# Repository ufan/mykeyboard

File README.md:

# A collection of designed keyboards #
## Features
All keyboards are powered by [zmk](https://zmk.dev/) with following design goals:
- portability
- minimalism
- ergonomic
- yet still powerful

## Super-powerful trackball firmware
- [youtube trackball demo](https://www.youtube.com/watch?v=7J-NTVMHwWQ&t=86s)
- [pmw3610_breakout pcb](https://github.com/ufan/pmw3610_breakout)
- [firmware support](https://github.com/ufan/zmk/tree/ptdevice-refactor)

# 42-key classic Corne-Pro with EPD display

# 34-key Sweep-Pro with horizontal encoders

# 32-key Blade with a mini-trackball and a touchbar

# Customizable logo display

# Wireless charging option

# Tenting support

# Extensible

# 3D-printed concave/convex keycaps

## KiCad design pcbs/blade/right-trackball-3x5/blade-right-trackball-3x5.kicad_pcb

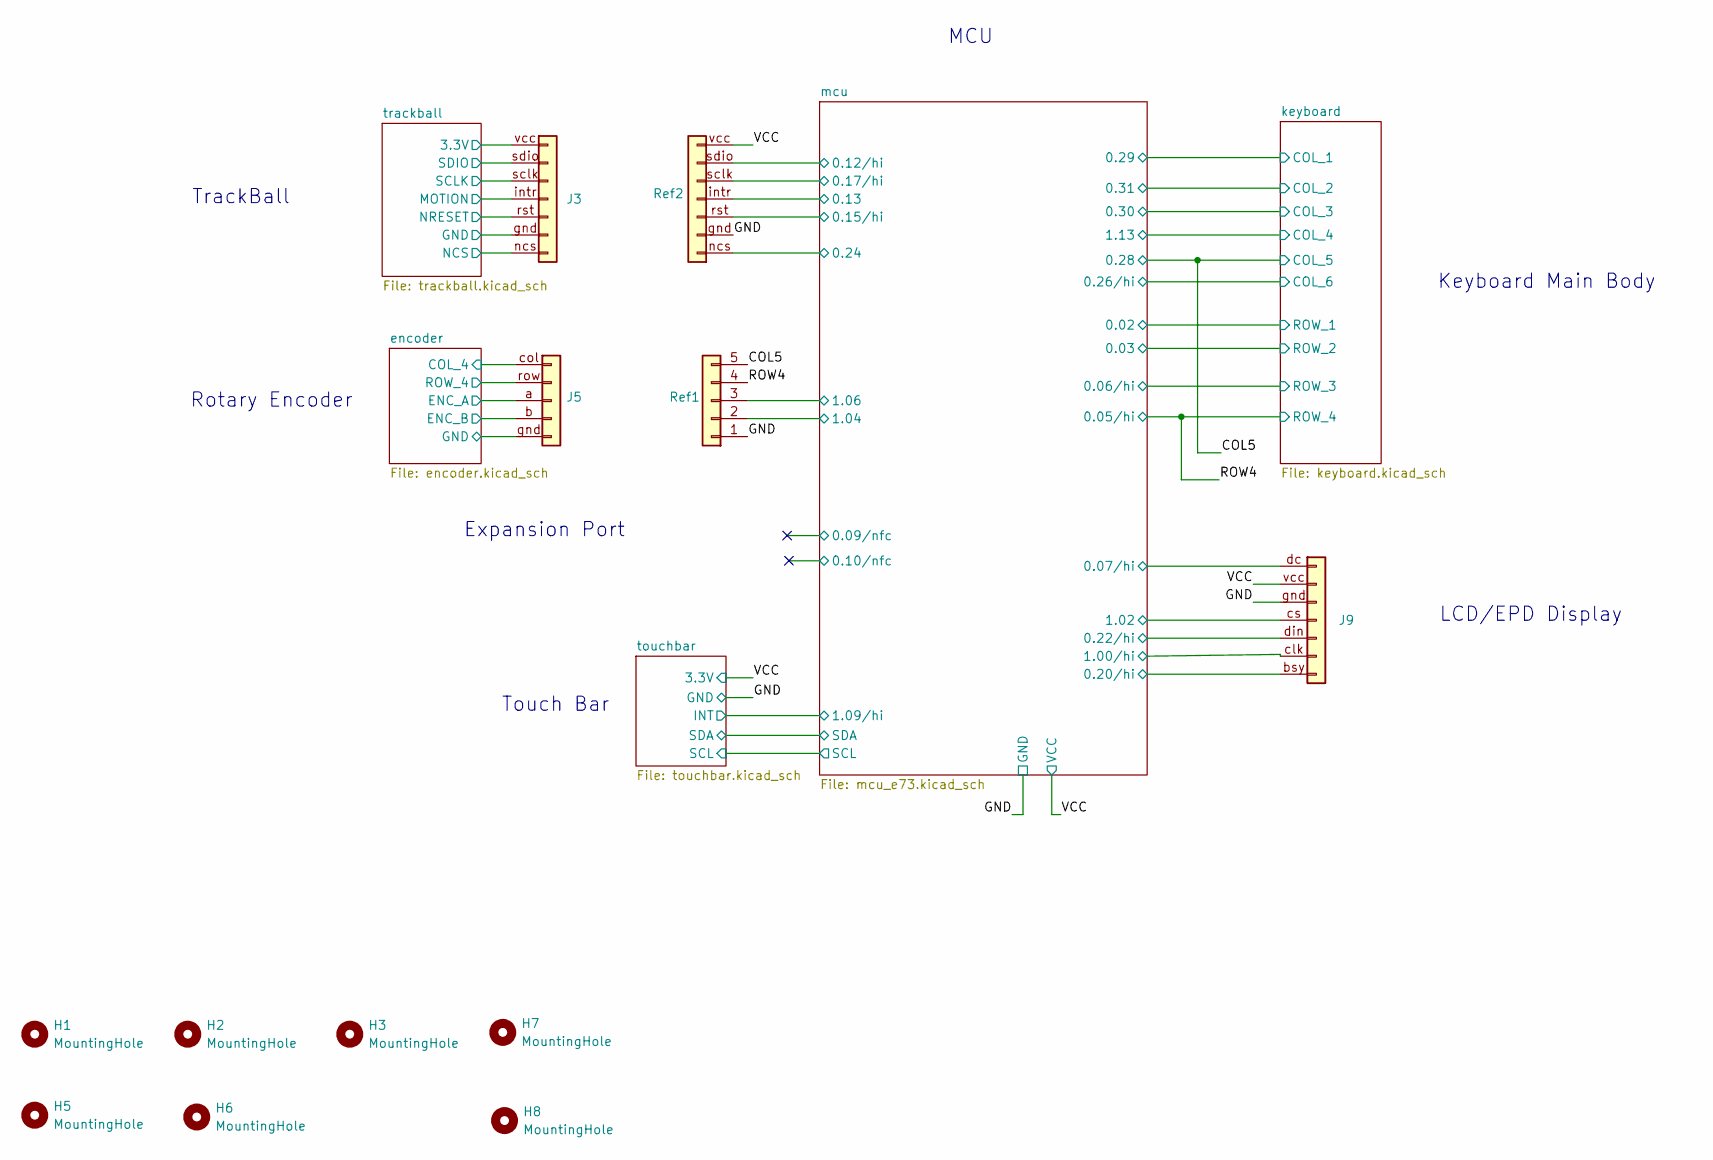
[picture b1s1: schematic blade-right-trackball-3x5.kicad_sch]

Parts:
H1, H2, H3, H5, H6, H7: MountingHole; MountingHole_3.2mm_M3_DIN965
H8: MountingHole; MountingHole_2mm
J3: Conn_01x07; PMW3610-Ref-Male
J5: Conn_01x05; Panasonic_EVQWGD001_Ref_Male
J9: Conn_Display_general; Conn_Display_MountHole
Ref1: Conn_01x05; Panasonic_EVQWGD001_Ref
Ref2: Conn_1x07; PMW3610-Ref

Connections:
/COL5: Ref1.5; also elsewhere on the board
/ROW4: Ref1.4; also elsewhere on the board
/VCC: J9.vcc, Ref2.vcc; also elsewhere on the board
/encoder/COL_4: J5.col; also elsewhere on the board
/encoder/ENC_A: J5.a; also elsewhere on the board
/encoder/ENC_B: J5.b; also elsewhere on the board
/encoder/GND: J5.gnd; also elsewhere on the board
/encoder/ROW_4: J5.row; also elsewhere on the board
/mcu/0.07/hi: J9.dc; also elsewhere on the board
/mcu/0.12/hi: Ref2.sdio; also elsewhere on the board
/mcu/0.13: Ref2.intr (motion); also elsewhere on the board
/mcu/0.15/hi: Ref2.rst; also elsewhere on the board
/mcu/0.17/hi: Ref2.sclk; also elsewhere on the board
/mcu/0.20/hi: J9.bsy; also elsewhere on the board
/mcu/0.22/hi: J9.din; also elsewhere on the board
/mcu/0.24: Ref2.ncs; also elsewhere on the board
/mcu/1.00/hi: J9.clk; also elsewhere on the board
/mcu/1.02: J9.cs; also elsewhere on the board
/mcu/1.04: Ref1.2; also elsewhere on the board
/mcu/1.06: Ref1.3; also elsewhere on the board
/trackball/3.3V: J3.vcc; also elsewhere on the board
/trackball/GND: J3.gnd; also elsewhere on the board
/trackball/MOTION: J3.intr (motion); also elsewhere on the board
/trackball/NCS: J3.ncs; also elsewhere on the board
/trackball/NRESET: J3.rst; also elsewhere on the board
/trackball/SCLK: J3.sclk; also elsewhere on the board
/trackball/SDIO: J3.sdio; also elsewhere on the board
GND: J9.gnd, Ref1.1, Ref2.gnd; also elsewhere on the board

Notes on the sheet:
Touch Bar
Rotary Encoder
LCD/EPD Display
Keyboard Main Body
Expansion Port
TrackBall
MCU

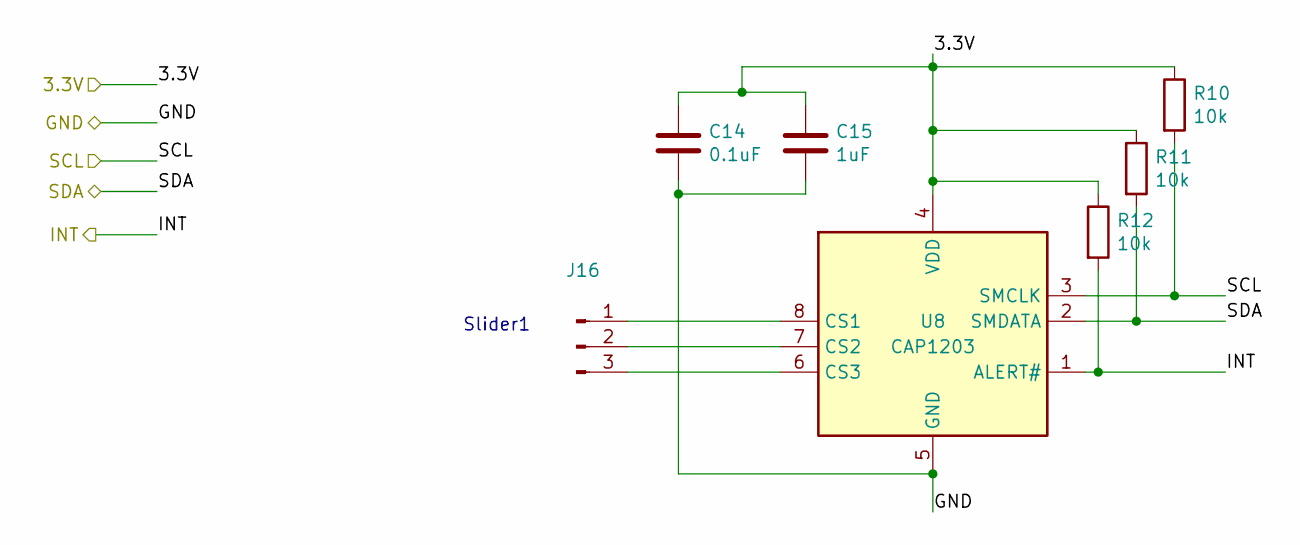
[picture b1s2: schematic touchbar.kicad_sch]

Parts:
C14: 0.1uF; C_0603_1608Metric
C15: 1uF; C_0603_1608Metric
J16: Conn_01x03_Male; TouchSlider-3_36x12mm
R10, R11, R12: 10k; R_0603_1608Metric
U8: CAP1203; SOIC-8_3.9x4.9mm_P1.27mm

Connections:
/VCC: C14.1, C15.1, R10.1, R11.1, R12.1, U8.4 (VDD); also elsewhere on the board
/mcu/SCL: R10.2, U8.3 (SMCLK); also elsewhere on the board
/mcu/SDA: R11.2, U8.2 (SMDATA); also elsewhere on the board
/touchbar/INT: R12.2, U8.1 (ALERT#); also elsewhere on the board
GND: C14.2, C15.2, U8.5 (GND); also elsewhere on the board
unnamed: J16.1, U8.8 (CS1)
unnamed: J16.2, U8.7 (CS2)
unnamed: J16.3, U8.6 (CS3)

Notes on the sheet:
Slider1

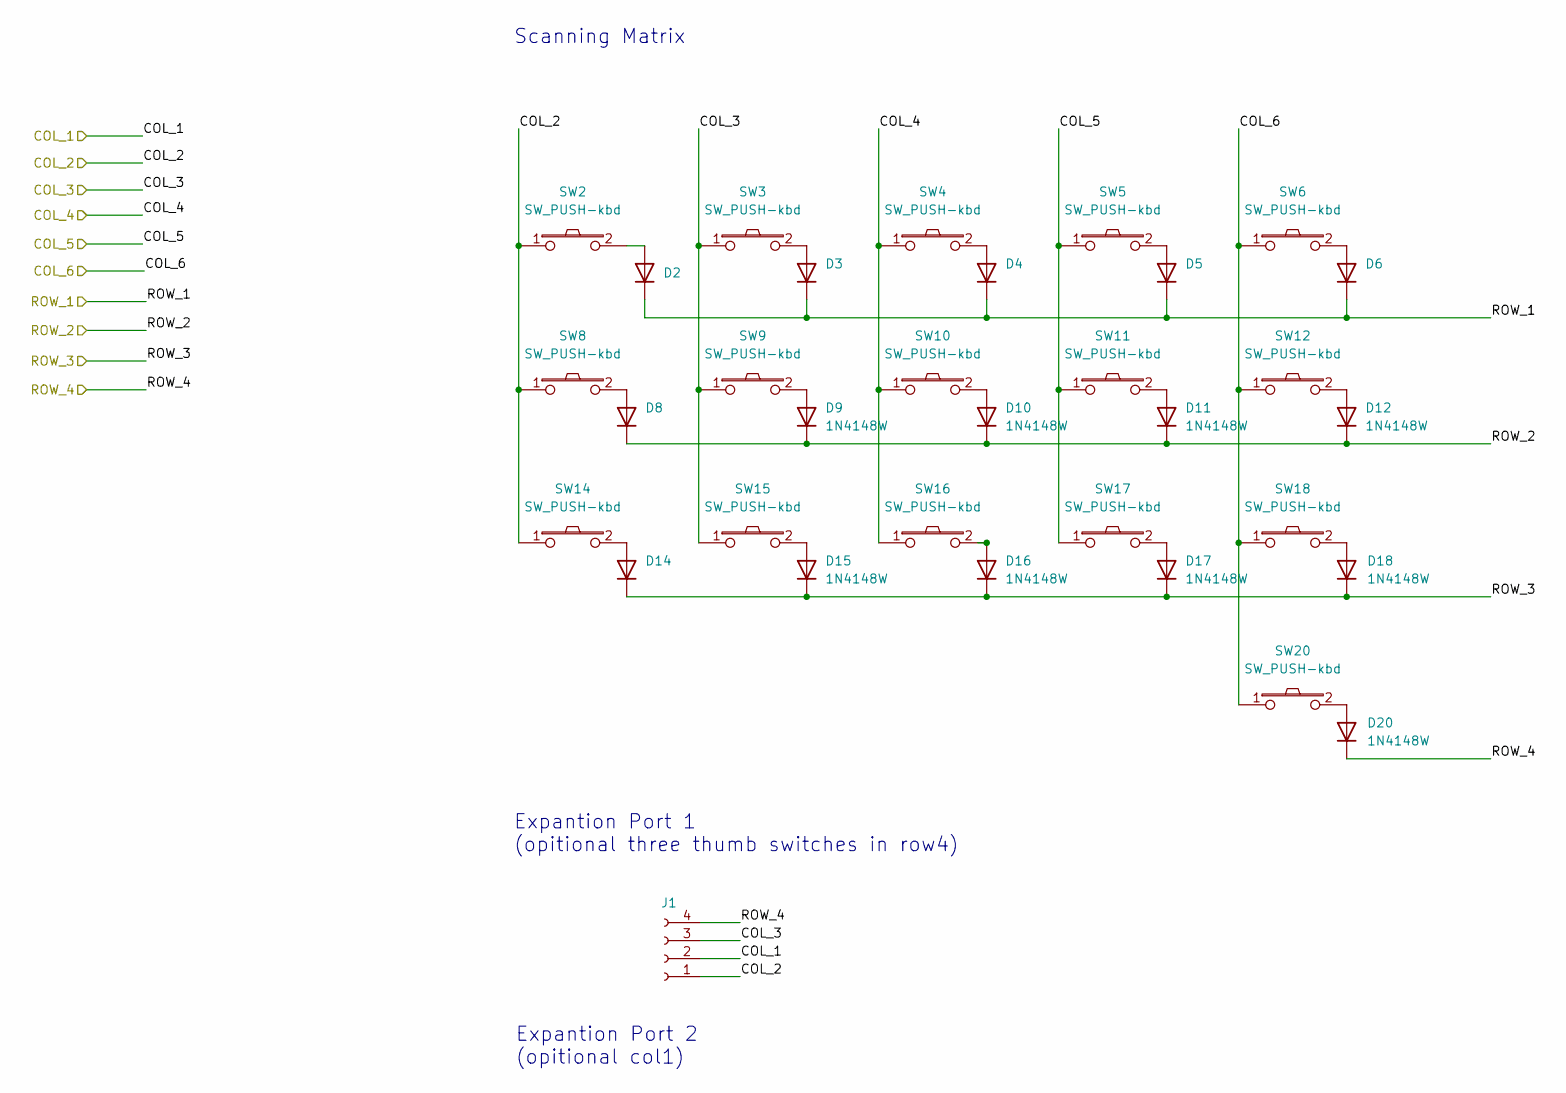
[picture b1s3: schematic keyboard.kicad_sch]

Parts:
D2, D3, D4, D5, D6, D8, D9, D10, D11, D12, D14, D15, D16, D17, D18, D20: 1N4148W; Diode
J1: expantion1; Magnetic-PogoPin-1x04-Female
SW2, SW3, SW4, SW5, SW6, SW8, SW9, SW10, SW11, SW12, SW14, SW15, SW16, SW17, SW18, SW20: SW_PUSH-kbd; Kailh_Choc_Hotplug

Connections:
/COL5: SW5.1, SW11.1, SW17.1; also elsewhere on the board
/ROW4: D20.1 (K), J1.4; also elsewhere on the board
/keyboard/COL_1: J1.2; also elsewhere on the board
/keyboard/COL_2: J1.1, SW2.1, SW8.1, SW14.1; also elsewhere on the board
/keyboard/COL_3: J1.3, SW3.1, SW9.1, SW15.1; also elsewhere on the board
/keyboard/COL_4: SW4.1, SW10.1, SW16.1; also elsewhere on the board
/keyboard/COL_6: SW6.1, SW12.1, SW18.1, SW20.1; also elsewhere on the board
/keyboard/ROW_1: D2.1 (K), D3.1 (K), D4.1 (K), D5.1 (K), D6.1 (K); also elsewhere on the board
/keyboard/ROW_2: D8.1 (K), D9.1 (K), D10.1 (K), D11.1 (K), D12.1 (K); also elsewhere on the board
/keyboard/ROW_3: D14.1 (K), D15.1 (K), D16.1 (K), D17.1 (K), D18.1 (K); also elsewhere on the board
unnamed: D2.2 (A), SW2.2
unnamed: D3.2 (A), SW3.2
unnamed: D4.2 (A), SW4.2
unnamed: D5.2 (A), SW5.2
unnamed: D6.2 (A), SW6.2
unnamed: D8.2 (A), SW8.2
unnamed: D9.2 (A), SW9.2
unnamed: D10.2 (A), SW10.2
unnamed: D11.2 (A), SW11.2
unnamed: D12.2 (A), SW12.2
unnamed: D14.2 (A), SW14.2
unnamed: D15.2 (A), SW15.2
unnamed: D16.2 (A), SW16.2
unnamed: D17.2 (A), SW17.2
unnamed: D18.2 (A), SW18.2
unnamed: D20.2 (A), SW20.2

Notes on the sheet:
Scanning Matrix
Expantion Port 2 (opitional col1)
Expantion Port 1 (opitional three thumb switches in row4)

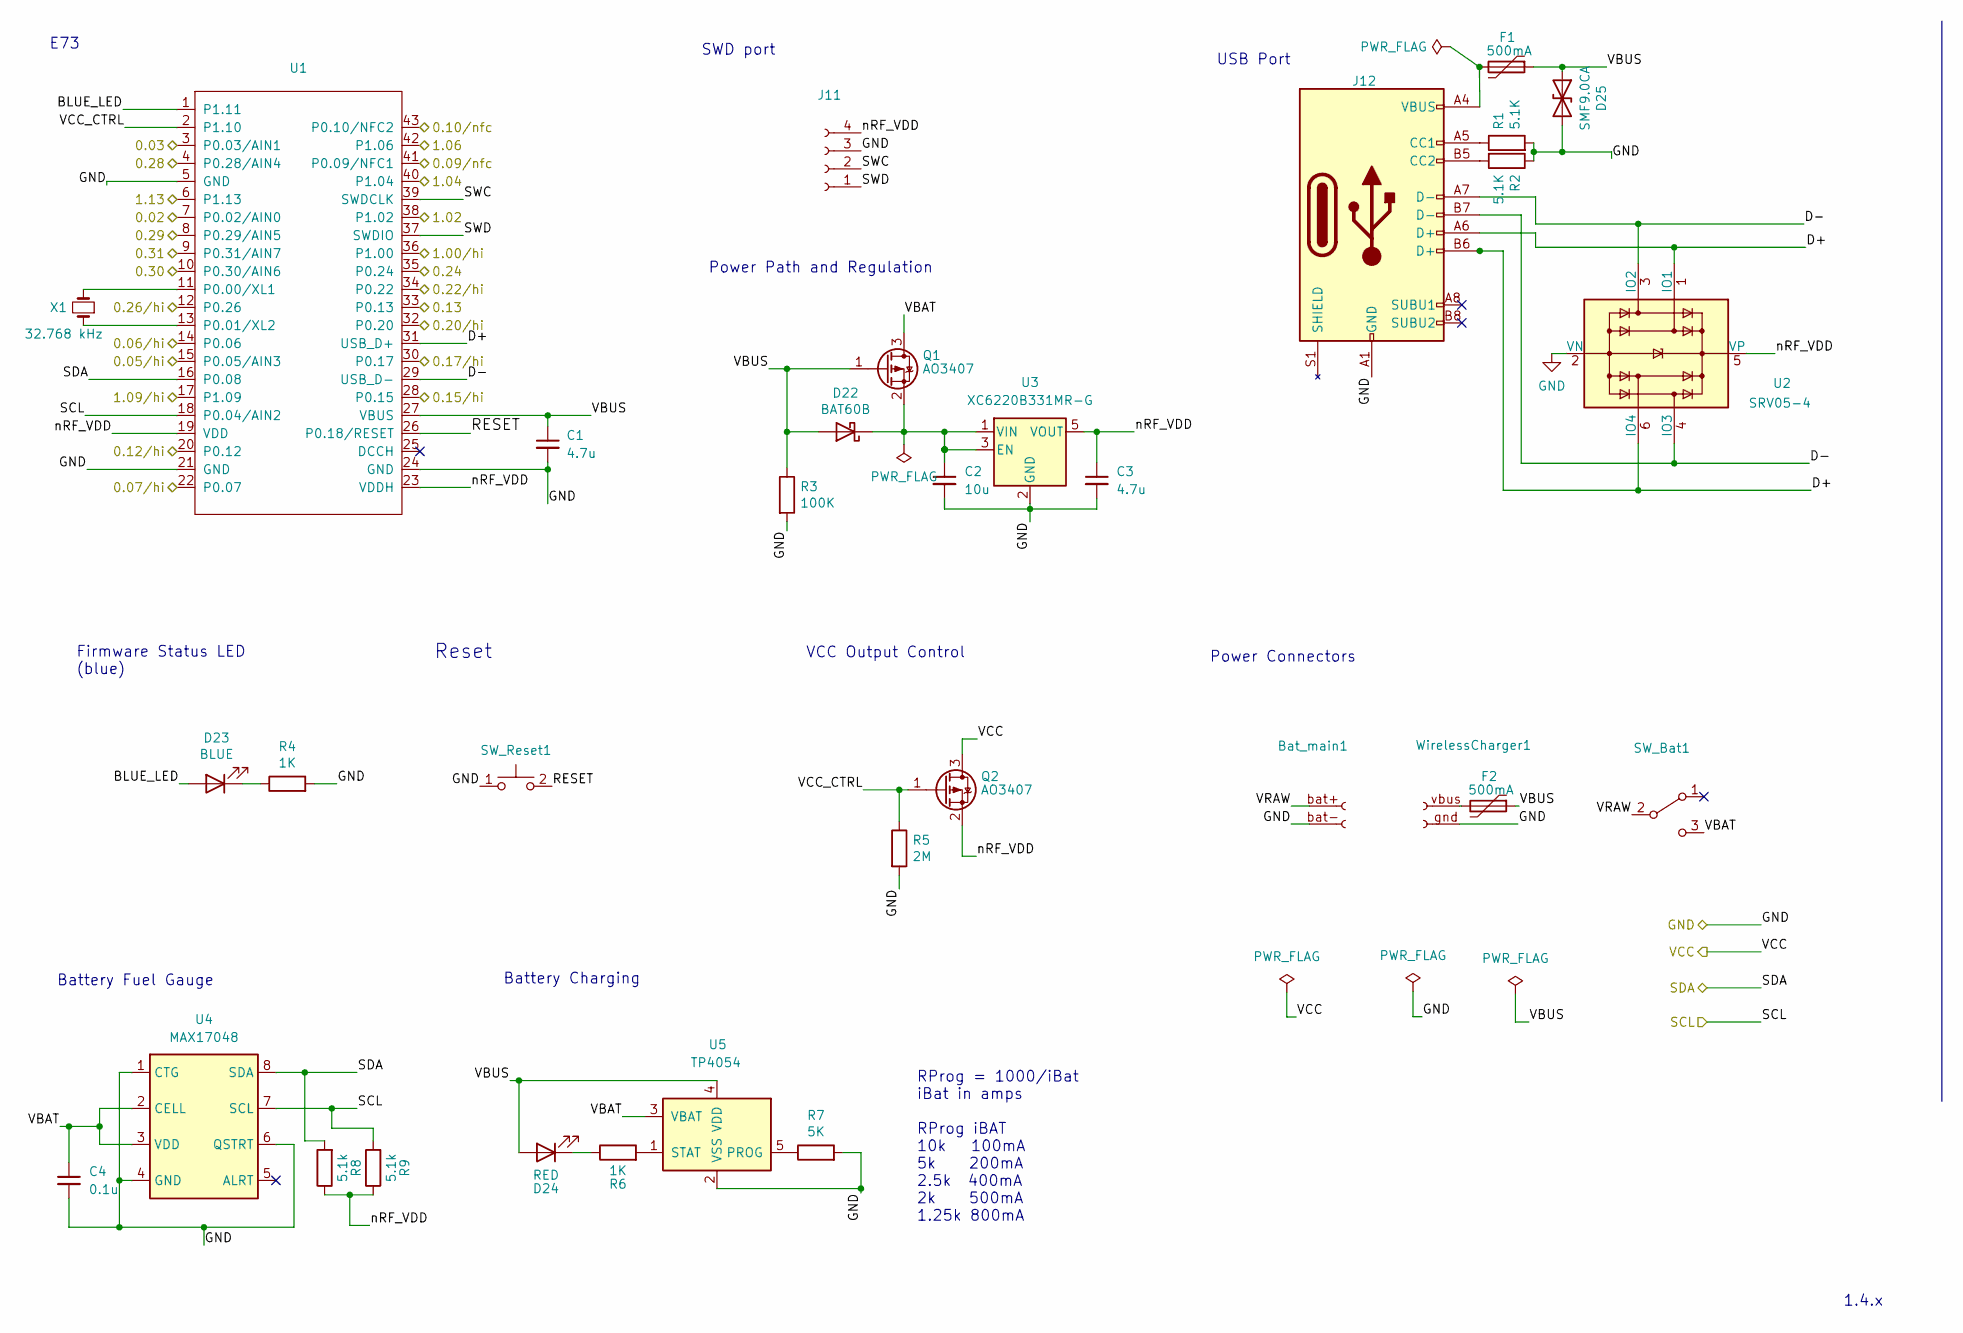
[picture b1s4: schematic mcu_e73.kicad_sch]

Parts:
Bat_main1: Conn_Battery_solderable; JST_ACH_BM02B-ACHSS-GAN-ETF_1x02-1MP_P1.20mm_Vertical
C1, C3: 4.7u; C_0603_1608Metric
C2: 10u; C_0603_1608Metric
C4: 0.1u; C_0603_1608Metric
D22: BAT60B; D_SOD-323
D23: BLUE; LED_0603_1608Metric
D24: RED; LED_0603_1608Metric
D25: SMF9.0CA; D_SOD-123F; Part Name Bidirectional Diode; LCSC Part C435473
F1, F2: 500mA; Fuse_1206_3216Metric; Part Name Polyfuse; LCSC Part C151162
J11: Conn_01x04_Female; PinHeader_1x04_P2.54mm_Vertical
J12: USB-C USB 2.0 MC-372; nrfmicro_USB-C_C168688
Q1, Q2: AO3407; SOT-23
R1, R2: 5.1K; R_0603_1608Metric
R3: 100K; R_0603_1608Metric
R4, R6: 1K; R_0603_1608Metric
R5: 2M; R_0603_1608Metric
R7: 5K; R_0603_1608Metric
R8, R9: 5.1k; R_0603_1608Metric
SW_Bat1: SW_Battery-kbd; SW_BSI10
SW_Reset1: SW_RESET-kbd; SW_Reset_vertical
U1: E73-2G4M08S1C; E73-2G4M08S1C-52840
U2: SRV05-4; Part Name TVS Diode Array; LCSC Part C558418
U3: XC6220B331MR-G; SOT-23-5
U4: MAX17048; MAX17048-TDFN-8-1EP_2x2mm_P0.5mm_EP0.8x1.2mm
U5: TP4054; SOT-23-5
WirelessCharger1: Conn_01x02_Female; JST_ACH_BM02B-ACHSS-GAN-ETF_1x02-1MP_P1.20mm_Vertical
X1: 32.768 kHz; Crystal_SMD_MicroCrystal_CM9V-T1A-2Pin_1.6x1.0mm

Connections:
/COL5: U1.4 (P0.28/AIN4); also elsewhere on the board
/ROW4: U1.15 (P0.05/AIN3); also elsewhere on the board
/VCC: Q2.3 (D); also elsewhere on the board
/keyboard/COL_1: U1.8 (P0.29/AIN5); also elsewhere on the board
/keyboard/COL_2: U1.9 (P0.31/AIN7); also elsewhere on the board
/keyboard/COL_3: U1.10 (P0.30/AIN6); also elsewhere on the board
/keyboard/COL_4: U1.6 (P1.13); also elsewhere on the board
/keyboard/COL_6: U1.12 (P0.26); also elsewhere on the board
/keyboard/ROW_1: U1.7 (P0.02/AIN0); also elsewhere on the board
/keyboard/ROW_2: U1.3 (P0.03/AIN1); also elsewhere on the board
/keyboard/ROW_3: U1.14 (P0.06); also elsewhere on the board
/mcu/0.07/hi: U1.22 (P0.07); also elsewhere on the board
/mcu/0.09/nfc: U1.41 (P0.09/NFC1)
/mcu/0.10/nfc: U1.43 (P0.10/NFC2)
/mcu/0.12/hi: U1.20 (P0.12); also elsewhere on the board
/mcu/0.13: U1.33 (P0.13); also elsewhere on the board
/mcu/0.15/hi: U1.28 (P0.15); also elsewhere on the board
/mcu/0.17/hi: U1.30 (P0.17); also elsewhere on the board
/mcu/0.20/hi: U1.32 (P0.20); also elsewhere on the board
/mcu/0.22/hi: U1.34 (P0.22); also elsewhere on the board
/mcu/0.24: U1.35 (P0.24); also elsewhere on the board
/mcu/1.00/hi: U1.36 (P1.00); also elsewhere on the board
/mcu/1.02: U1.38 (P1.02); also elsewhere on the board
/mcu/1.04: U1.40 (P1.04); also elsewhere on the board
/mcu/1.06: U1.42 (P1.06); also elsewhere on the board
/mcu/BLUE_LED: D23.2 (A), U1.1 (P1.11)
/mcu/D+: J12.A6 (D+), J12.B6 (D+), U1.31 (USB_D+), U2.1 (IO1), U2.6 (IO4)
/mcu/D-: J12.A7 (D-), J12.B7 (D-), U1.29 (USB_D-), U2.3 (IO2), U2.4 (IO3)
/mcu/RESET: SW_Reset1.2, U1.26 (P0.18/RESET)
/mcu/SCL: R9.2, U1.18 (P0.04/AIN2), U4.7 (SCL); also elsewhere on the board
/mcu/SDA: R8.2, U1.16 (P0.08), U4.8 (SDA); also elsewhere on the board
/mcu/SWC: J11.2, U1.39 (SWDCLK)
/mcu/SWD: J11.1, U1.37 (SWDIO)
/mcu/VBAT: C4.1, Q1.3 (D), SW_Bat1.3 (C), U4.2 (CELL), U4.3 (VDD), U5.3 (VBAT)
/mcu/VBUS: C1.1, D22.2 (A), D24.2 (A), D25.1 (A1), F1.1, F2.1, Q1.1 (G), R3.1, U1.27 (VBUS), U5.4 (VDD)
/mcu/VCC_CTRL: Q2.1 (G), R5.1, U1.2 (P1.10)
/mcu/VRAW: Bat_main1.bat+ (Bat+), SW_Bat1.2 (B)
/mcu/nRF_VDD: C3.1, J11.4, Q2.2 (S), R8.1, R9.1, U1.19 (VDD), U1.23 (VDDH), U2.5 (VP), U3.5 (VOUT)
/touchbar/INT: U1.17 (P1.09); also elsewhere on the board
GND: Bat_main1.bat- (Bat-), C1.2, C2.2, C3.2, C4.2, D25.2 (A2), J11.3, J12.A1 (GND), R1.2, R2.1, R3.2, R4.2, R5.2, R7.2, SW_Reset1.1, U1.5 (GND), U1.21 (GND), U1.24 (GND), U2.2 (VN), U3.2 (GND), U4.1 (CTG), U4.4 (GND), U4.6 (QSTRT), U5.2 (VSS), WirelessCharger1.gnd; also elsewhere on the board
unnamed: C2.1, D22.1 (K), Q1.2 (S), U3.1 (VIN), U3.3 (EN)
unnamed: D23.1 (K), R4.1
unnamed: D24.1 (K), R6.1
unnamed: F1.2, J12.A4 (VBUS)
unnamed: F2.2, WirelessCharger1.vbus
unnamed: J12.A5 (CC1), R1.1
unnamed: J12.B5 (CC2), R2.2
unnamed: R6.2, U5.1 (STAT)
unnamed: R7.1, U5.5 (PROG)
unnamed: U1.11 (P0.00/XL1), X1.2
unnamed: U1.13 (P0.01/XL2), X1.1

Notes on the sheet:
Battery Charging
Reset
Power Path and Regulation
RProg = 1000/iBat iBat in amps RProg iBAT 10k 100mA 5k 200mA 2.5k 400mA 2k 500mA 1.25k 800mA
1.4.x
USB Port
Battery Fuel Gauge
E73
VCC Output Control
Power Connectors
SWD port
Firmware Status LED (blue)

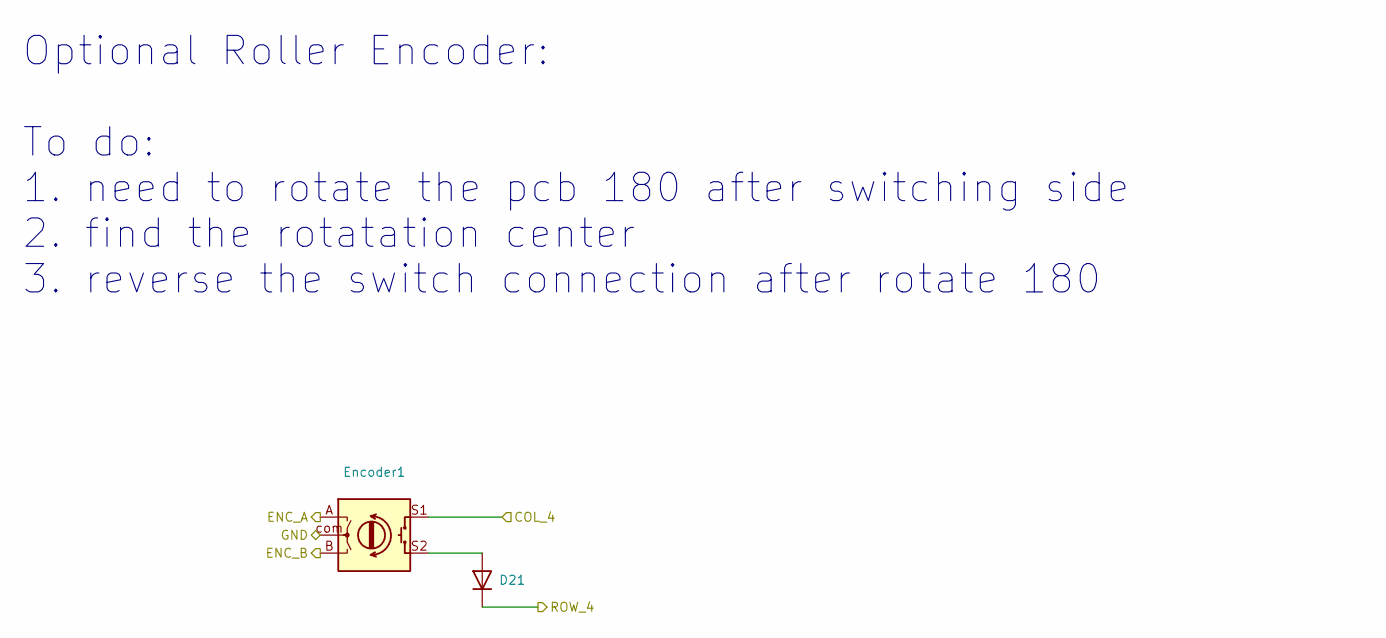
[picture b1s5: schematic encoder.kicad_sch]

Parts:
D21: 1N4148W; Diode
Encoder1: RotaryEncoder; Panasonic_EVQWGD001_Latest

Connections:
/encoder/COL_4: Encoder1.S1; also elsewhere on the board
/encoder/ENC_A: Encoder1.A; also elsewhere on the board
/encoder/ENC_B: Encoder1.B; also elsewhere on the board
/encoder/GND: Encoder1.com (COM); also elsewhere on the board
/encoder/ROW_4: D21.1 (K); also elsewhere on the board
unnamed: D21.2 (A), Encoder1.S2

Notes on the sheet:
Optional Roller Encoder: To do: 1. need to rotate the pcb 180 after switching side 2. find the rotatation center 3. reverse the switch connection after rotate 180

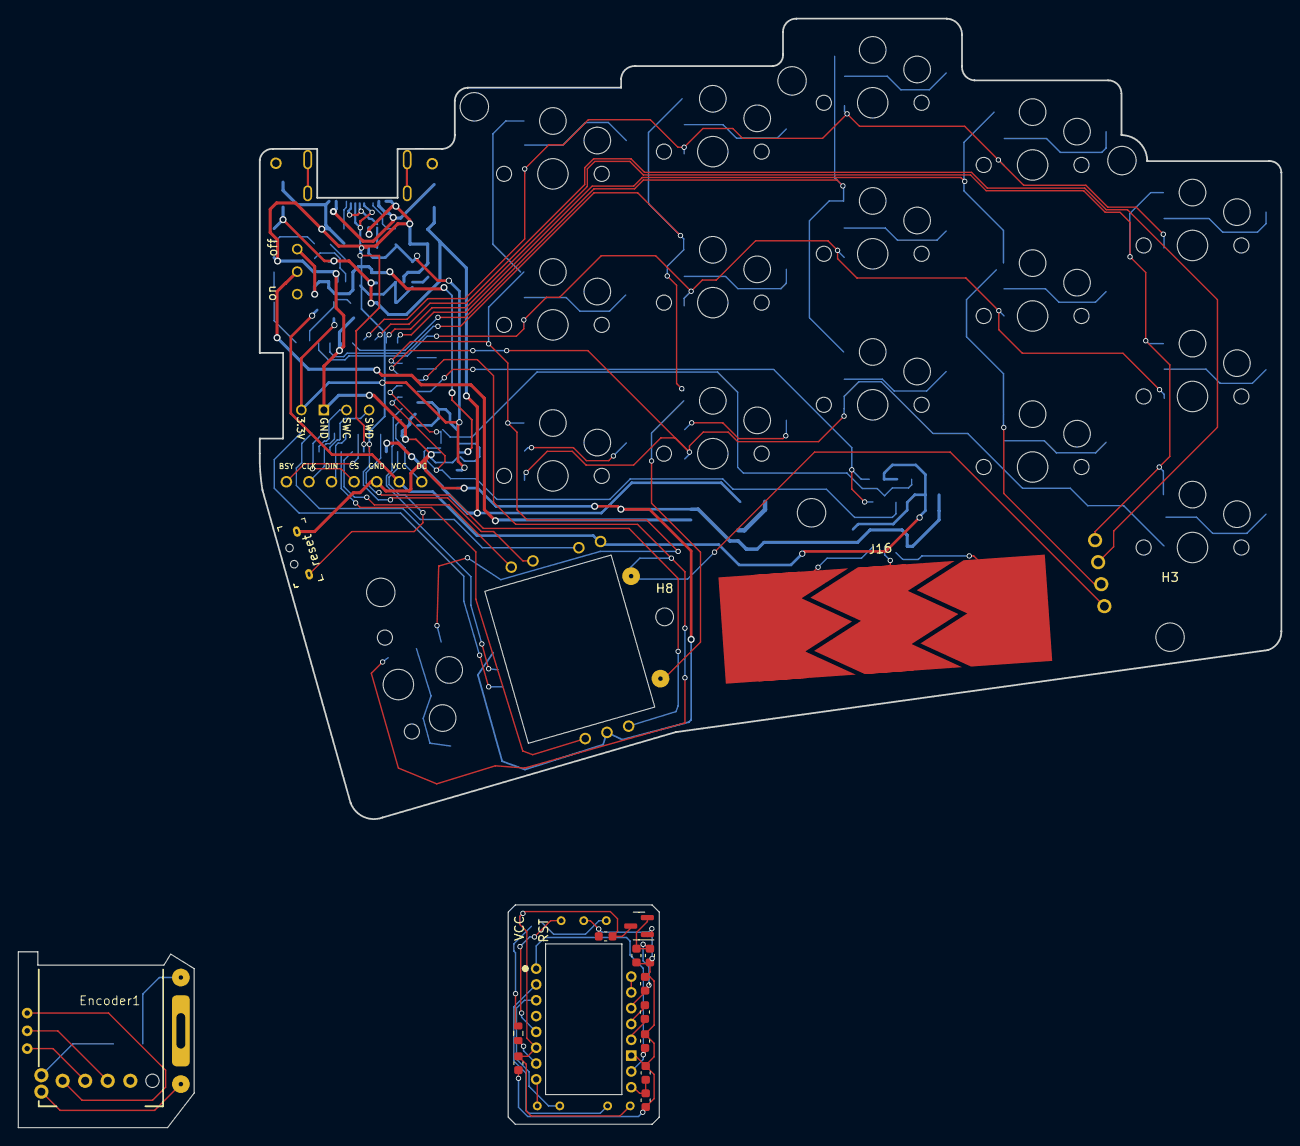
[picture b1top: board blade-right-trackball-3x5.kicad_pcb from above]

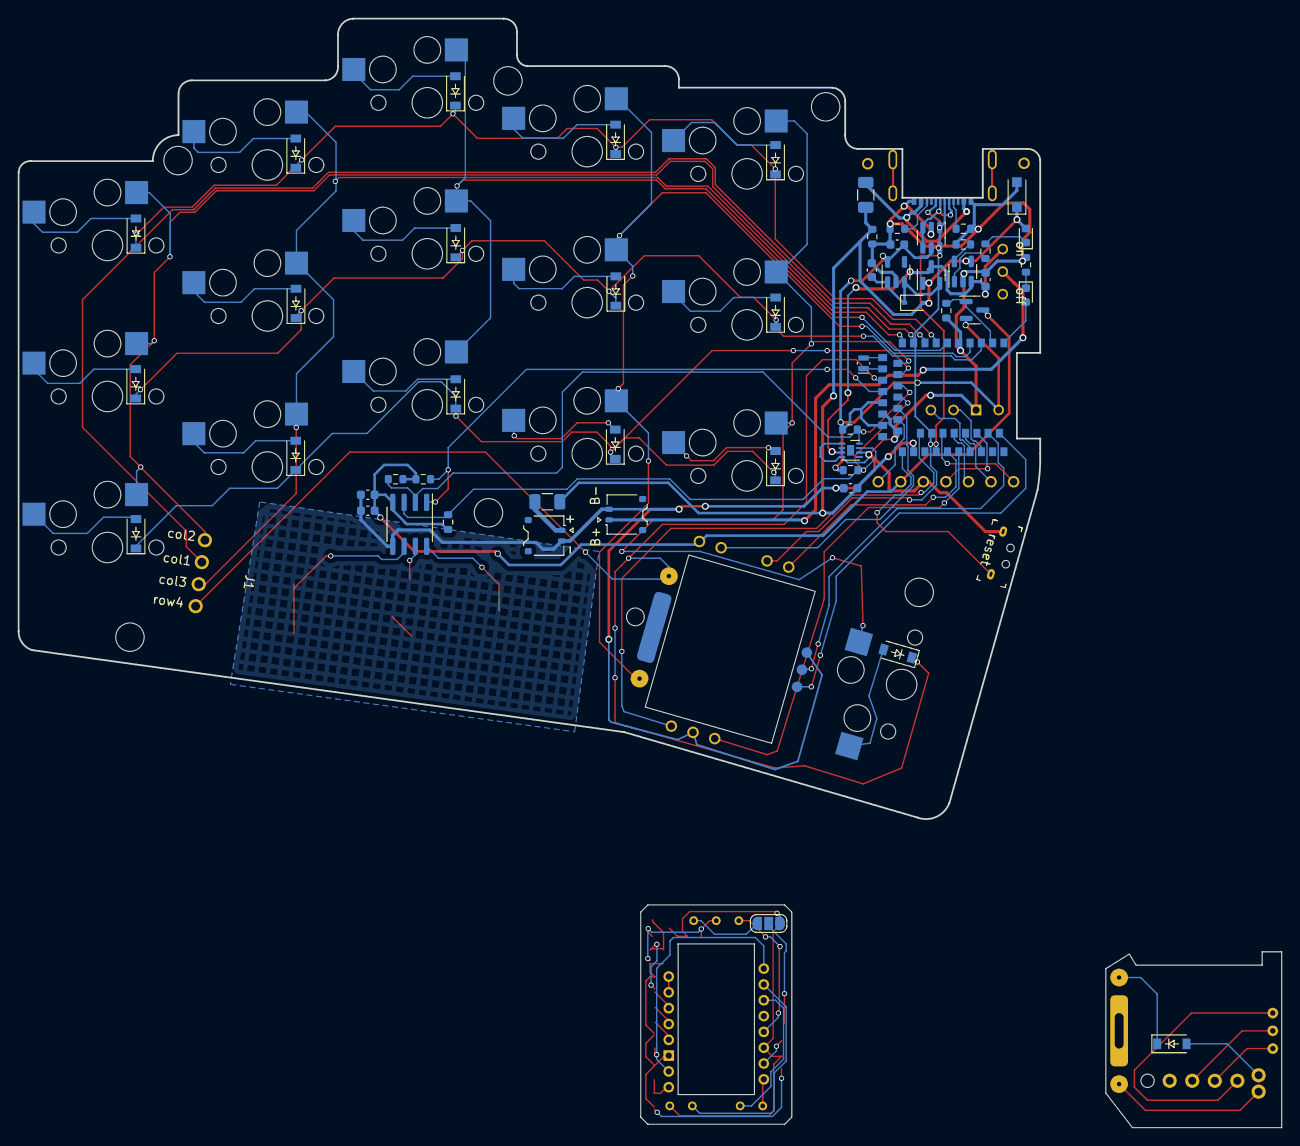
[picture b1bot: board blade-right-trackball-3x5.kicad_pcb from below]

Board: 2 copper layers, 115.0 x 90.1 mm, 100 parts (57 on the bottom side), 89 nets.

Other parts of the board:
C5: 10n; C_0603_1608Metric
C6, C11: 100n; C_0603_1608Metric
C7: 3.3u/16V; C_0603_1608Metric
C8: 100n (X7R); C_0603_1608Metric
C9, C10: 1u; C_0603_1608Metric
C12: 10u (X7R); C_0603_1608Metric
C13: 10n (X7R); C_0603_1608Metric
JP1: SolderJumper_3_Open; SolderJumper-3_P1.3mm_Open_RoundedPad1.0x1.5mm_NumberLabels
R13: 2M; R_0603_1608Metric
U6: PMW3610
U7: MCP1700-1802E-TT; SOT-23

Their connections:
/trackball/1.8V: C6.1, C7.1, C10.1, U6.14 (VDD), U7.2 (VO)
/trackball/3.3V: C9.2, C11.1, JP1.3 (B), U6.6 (VDDIO), U7.3 (VI); also elsewhere on the board
/trackball/GND: C5.2, C6.2, C7.2, C9.1, C10.2, C11.2, C12.2, C13.2, U6.11 (GND), U7.1 (GND); also elsewhere on the board
/trackball/MOTION: U6.8 (MOTION); also elsewhere on the board
/trackball/NCS: U6.5 (NCS); also elsewhere on the board
/trackball/NRESET: JP1.1 (A); also elsewhere on the board
/trackball/SCLK: U6.3 (SCLK); also elsewhere on the board
/trackball/SDIO: U6.2 (SDIO); also elsewhere on the board
unnamed: C5.1, U6.1 (+VCSEL), U6.10 (PASS_T)
unnamed: C8.1, U6.13 (CN)
unnamed: C8.2, U6.12 (CP)
unnamed: C12.1, C13.1, U6.9 (VCP)
unnamed: JP1.2 (C), R13.1
unnamed: R13.2, U6.7 (NRESET)
unnamed: U6.15 (XYLASER), U6.16 (-VCSEL)

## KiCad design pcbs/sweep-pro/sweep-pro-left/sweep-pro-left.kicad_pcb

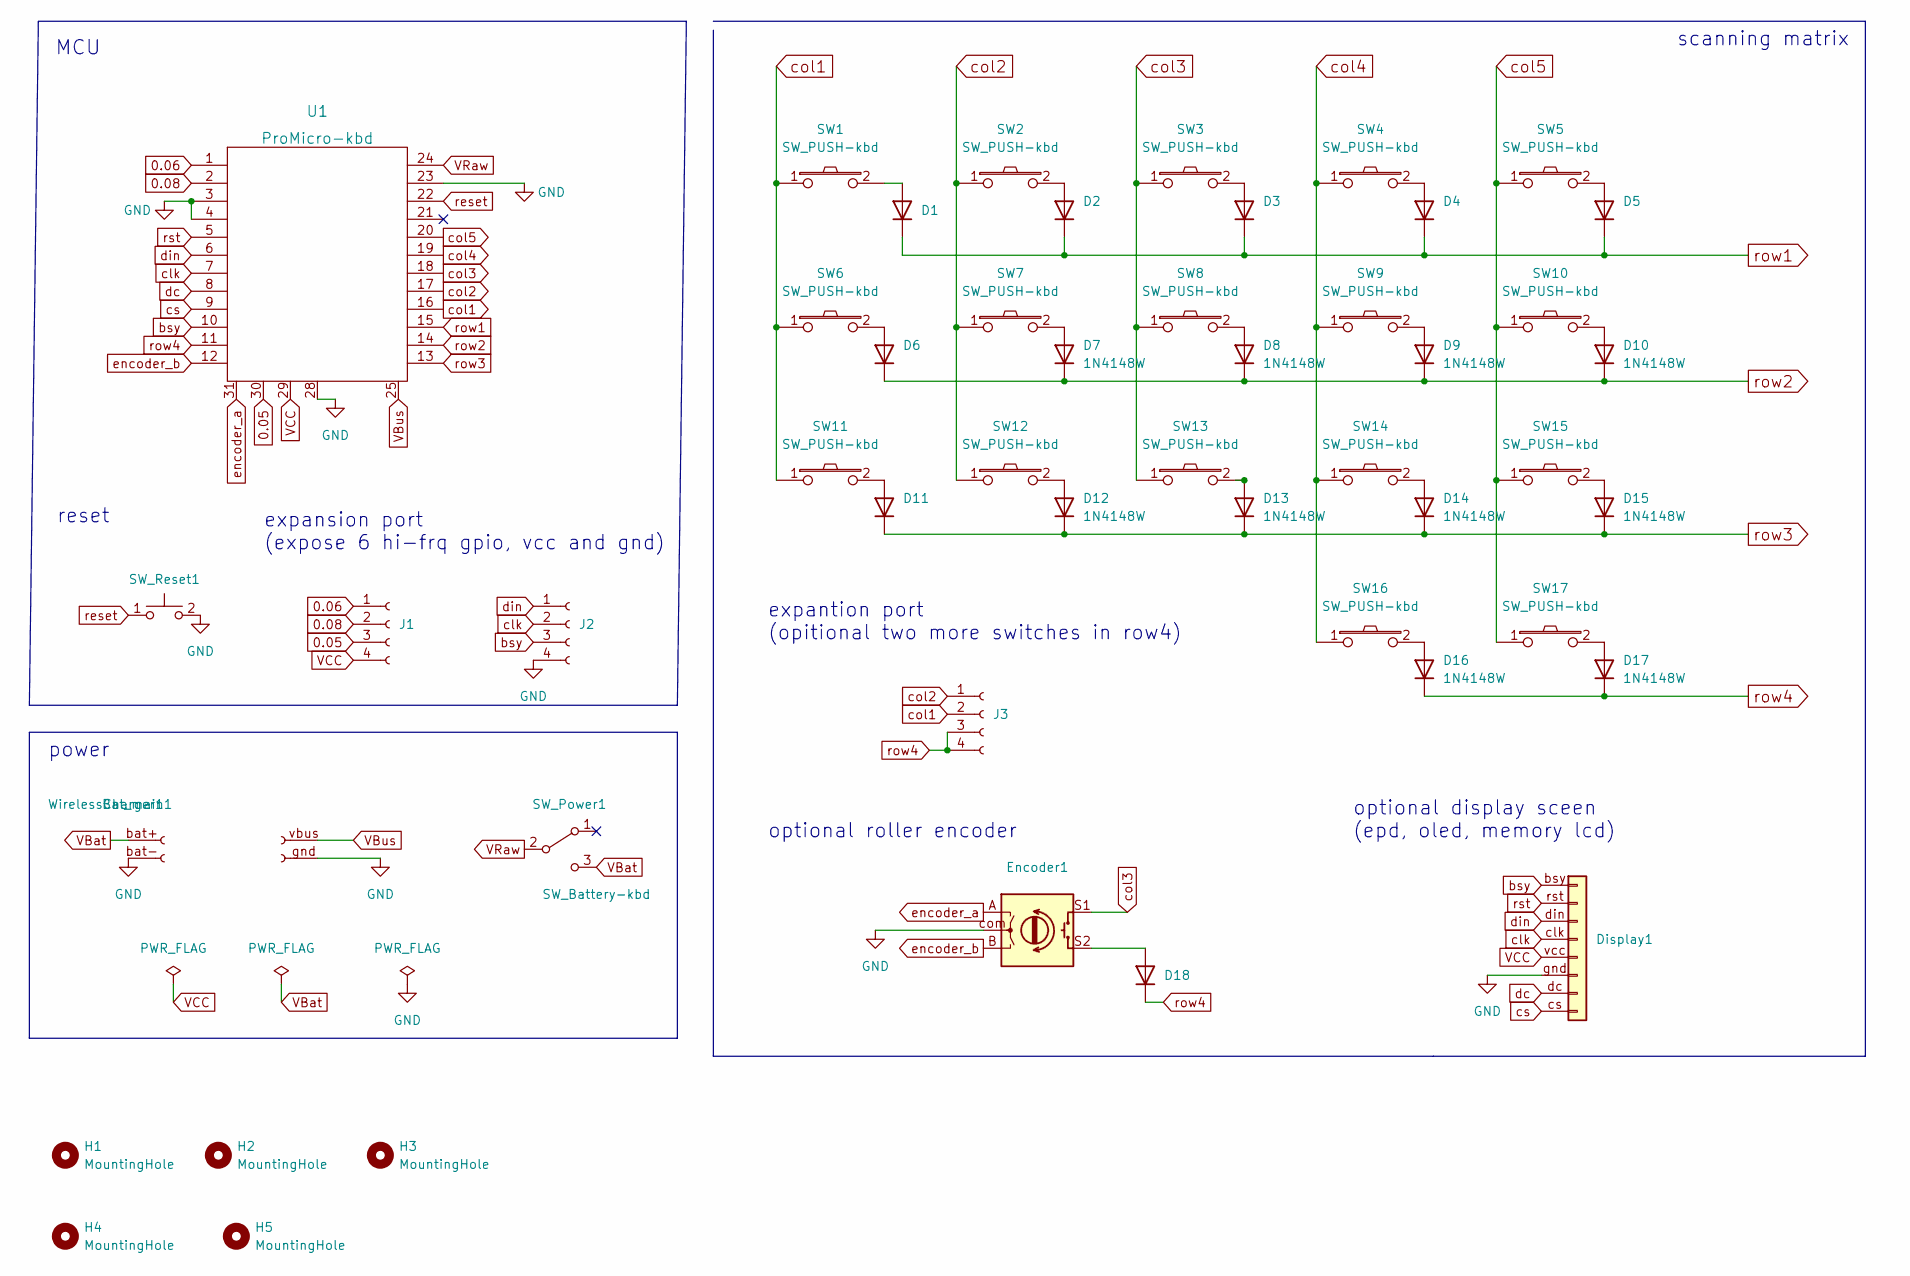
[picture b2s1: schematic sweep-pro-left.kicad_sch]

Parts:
Bat_main1: Conn_Battery_solderable; Molex_Panelmate_53780-0270_1x02-1MP_P1.25mm_Horizontal
D1, D2, D3, D4, D5, D6, D7, D8, D9, D10, D11, D12, D13, D14, D15, D16, D17, D18: 1N4148W; Diode
Display1: Conn_Display_general; Conn_EPD
Encoder1: RotaryEncoder; RollerEncoder_Panasonic_EVQWGD001
H1, H2, H3, H4, H5: MountingHole; MountingHole_3.2mm_M3_DIN965
J1, J2: Conn_01x04_Female; pogopin_1x4
J3: expantion1; pogopin_1x4
SW1, SW2, SW3, SW4, SW5, SW6, SW7, SW8, SW9, SW10, SW11, SW12, SW13, SW14, SW15, SW16, SW17: SW_PUSH-kbd; Kailh_Choc_Hotplug
SW_Power1: SW_Battery-kbd; SW_BSI10
SW_Reset1: SW_RESET-kbd; SW_Reset_vertical
U1: ProMicro-kbd; ProMacroLite_BackMount_Partial
WirelessCharger1: Conn_01x02_Female; VBus_pad_reversible

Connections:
0.05: J1.3, U1.30
0.06: J1.1, U1.1 (TX)
0.08: J1.2, U1.2 (RX)
GND: Bat_main1.bat- (Bat-), Display1.gnd (GND), Encoder1.com (COM), J2.4, SW_Reset1.2, U1.3 (GND), U1.4 (GND), U1.23 (GND), U1.28 (gnd), WirelessCharger1.gnd (GND)
unnamed: D1.2 (A), SW1.2
unnamed: D2.2 (A), SW2.2
unnamed: D3.2 (A), SW3.2
unnamed: D4.2 (A), SW4.2
unnamed: D5.2 (A), SW5.2
unnamed: D6.2 (A), SW6.2
unnamed: D7.2 (A), SW7.2
unnamed: D8.2 (A), SW8.2
unnamed: D9.2 (A), SW9.2
unnamed: D10.2 (A), SW10.2
unnamed: D11.2 (A), SW11.2
unnamed: D12.2 (A), SW12.2
unnamed: D13.2 (A), SW13.2
unnamed: D14.2 (A), SW14.2
unnamed: D15.2 (A), SW15.2
unnamed: D16.2 (A), SW16.2
unnamed: D17.2 (A), SW17.2
unnamed: D18.2 (A), Encoder1.S2
VBat: Bat_main1.bat+ (Bat+), SW_Power1.3 (C)
VBus: U1.25 (vbus), WirelessCharger1.vbus (VBUS)
VCC: Display1.vcc (VCC), J1.4, U1.29 (3.3V)
VRaw: SW_Power1.2 (B), U1.24 (RAW)
bsy: Display1.bsy (BSY), J2.3, U1.10 (E6)
clk: Display1.clk (CLK), J2.2, U1.7 (D4)
col1: J3.2, SW1.1, SW6.1, SW11.1, U1.16 (B1)
col2: J3.1, SW2.1, SW7.1, SW12.1, U1.17 (F7)
col3: Encoder1.S1, SW3.1, SW8.1, SW13.1, U1.18 (F6)
col4: SW4.1, SW9.1, SW14.1, SW16.1, U1.19 (F5)
col5: SW5.1, SW10.1, SW15.1, SW17.1, U1.20 (F4)
cs: Display1.cs (CS), U1.9 (D7)
dc: Display1.dc (DC), U1.8 (C6)
din: Display1.din (DIN), J2.1, U1.6 (SCL)
encoder_a: Encoder1.A, U1.31
encoder_b: Encoder1.B, U1.12 (B5)
reset: SW_Reset1.1, U1.22 (RST)
row1: D1.1 (K), D2.1 (K), D3.1 (K), D4.1 (K), D5.1 (K), U1.15 (B3)
row2: D6.1 (K), D7.1 (K), D8.1 (K), D9.1 (K), D10.1 (K), U1.14 (B2)
row3: D11.1 (K), D12.1 (K), D13.1 (K), D14.1 (K), D15.1 (K), U1.13 (B6)
row4: D16.1 (K), D17.1 (K), D18.1 (K), J3.3, J3.4, U1.11 (B4)
rst: Display1.rst (RST), U1.5 (SDA)

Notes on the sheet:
scanning matrix
optional roller encoder
reset
expansion port (expose 6 hi-frq gpio, vcc and gnd)
power
optional display sceen (epd, oled, memory lcd)
expantion port (opitional two more switches in row4)
MCU
